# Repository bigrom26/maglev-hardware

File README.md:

# maglev-hardware
KiCad schematic and PCB for maglev projects. See preview in `*.pdf` files.

## Theory
In terms of control systems' general theory there're 4 main components: object under control; actuators and drivers; controller itself; feedback loop. Applied to this magnetic levitation system, these components are:
  - Object: permanent magnet
  - Driver: almost this schematic plus PWM
  - Controller: PID algorithm executed by the MCU (see [maglev-ti-rtos](https://github.com/ussserrr/maglev-ti-rtos))
  - Feedback: Hall sensor
We specify setpoint (desired voltage depended on mutual arrangement of permanent and electro magnets) and get status of the process variable by Hall sensor (feedback value).

## Notes
Due to lack of some hardware solutions (such as H-bridge) this version of the device can only push and release permanent magnet and can't pull it.

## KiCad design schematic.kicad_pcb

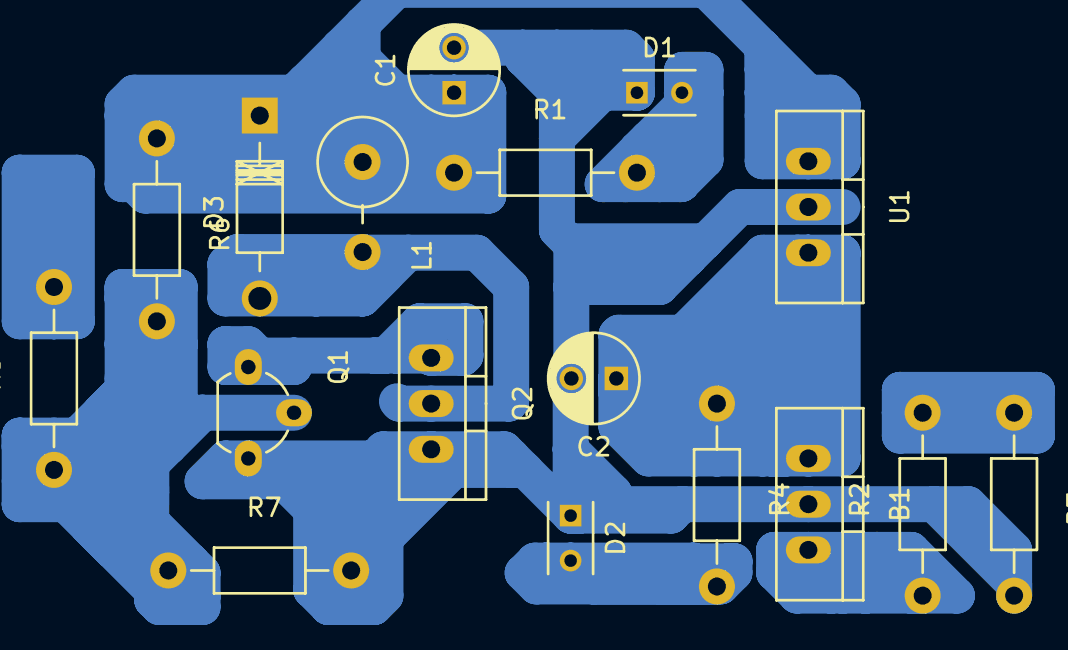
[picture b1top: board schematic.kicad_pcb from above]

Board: 2 copper layers, 17 parts (0 on the bottom side), 10 nets.

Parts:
B1: A1302; TO-220_Neutral123_Vertical
C1: 100u; C_Radial_D5_L6_P2.5
C2: 10u; C_Radial_D5_L6_P2.5
D1, D2: LED; C_Rect_L4_W2.5_P2.5
D3: 1N4004; Diode_DO-41_SOD81_Horizontal_RM10
L1: COIL; Resistor_Vertical_RM5mm
Q1: BC237; TO-92_Molded_Wide_Oval
Q2: IRF640; TO-220_Neutral123_Vertical
R1, R2, R3, R5, R6: 1k; Resistor_Horizontal_RM10mm
R4: 430; Resistor_Horizontal_RM10mm
R7: 10k; Resistor_Horizontal_RM10mm
U1: LM7805; TO-220_Neutral123_Vertical

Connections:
+5V: B1.1, C2.1, R4.1, U1.3
+12V: C1.1, D3.1, L1.1, R1.1, R6.1, U1.1
GND: B1.2, C1.2, C2.2, D1.1, D2.1, Q1.3, Q2.3, R3.2, R7.2, U1.2
unnamed: B1.3, R2.1
unnamed: D1.2, R1.2
unnamed: D2.2, R4.2
unnamed: D3.2, L1.2, Q2.2
unnamed: Q1.1, Q2.1
unnamed: Q1.2, R5.1, R6.2, R7.1
PE3: R2.2, R3.1
